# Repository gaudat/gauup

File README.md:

# Gaudat's GauUp
---

A collection of my rambling (GauUping). Expect unstructured mind-dump with project-logging and blogging mixed in.

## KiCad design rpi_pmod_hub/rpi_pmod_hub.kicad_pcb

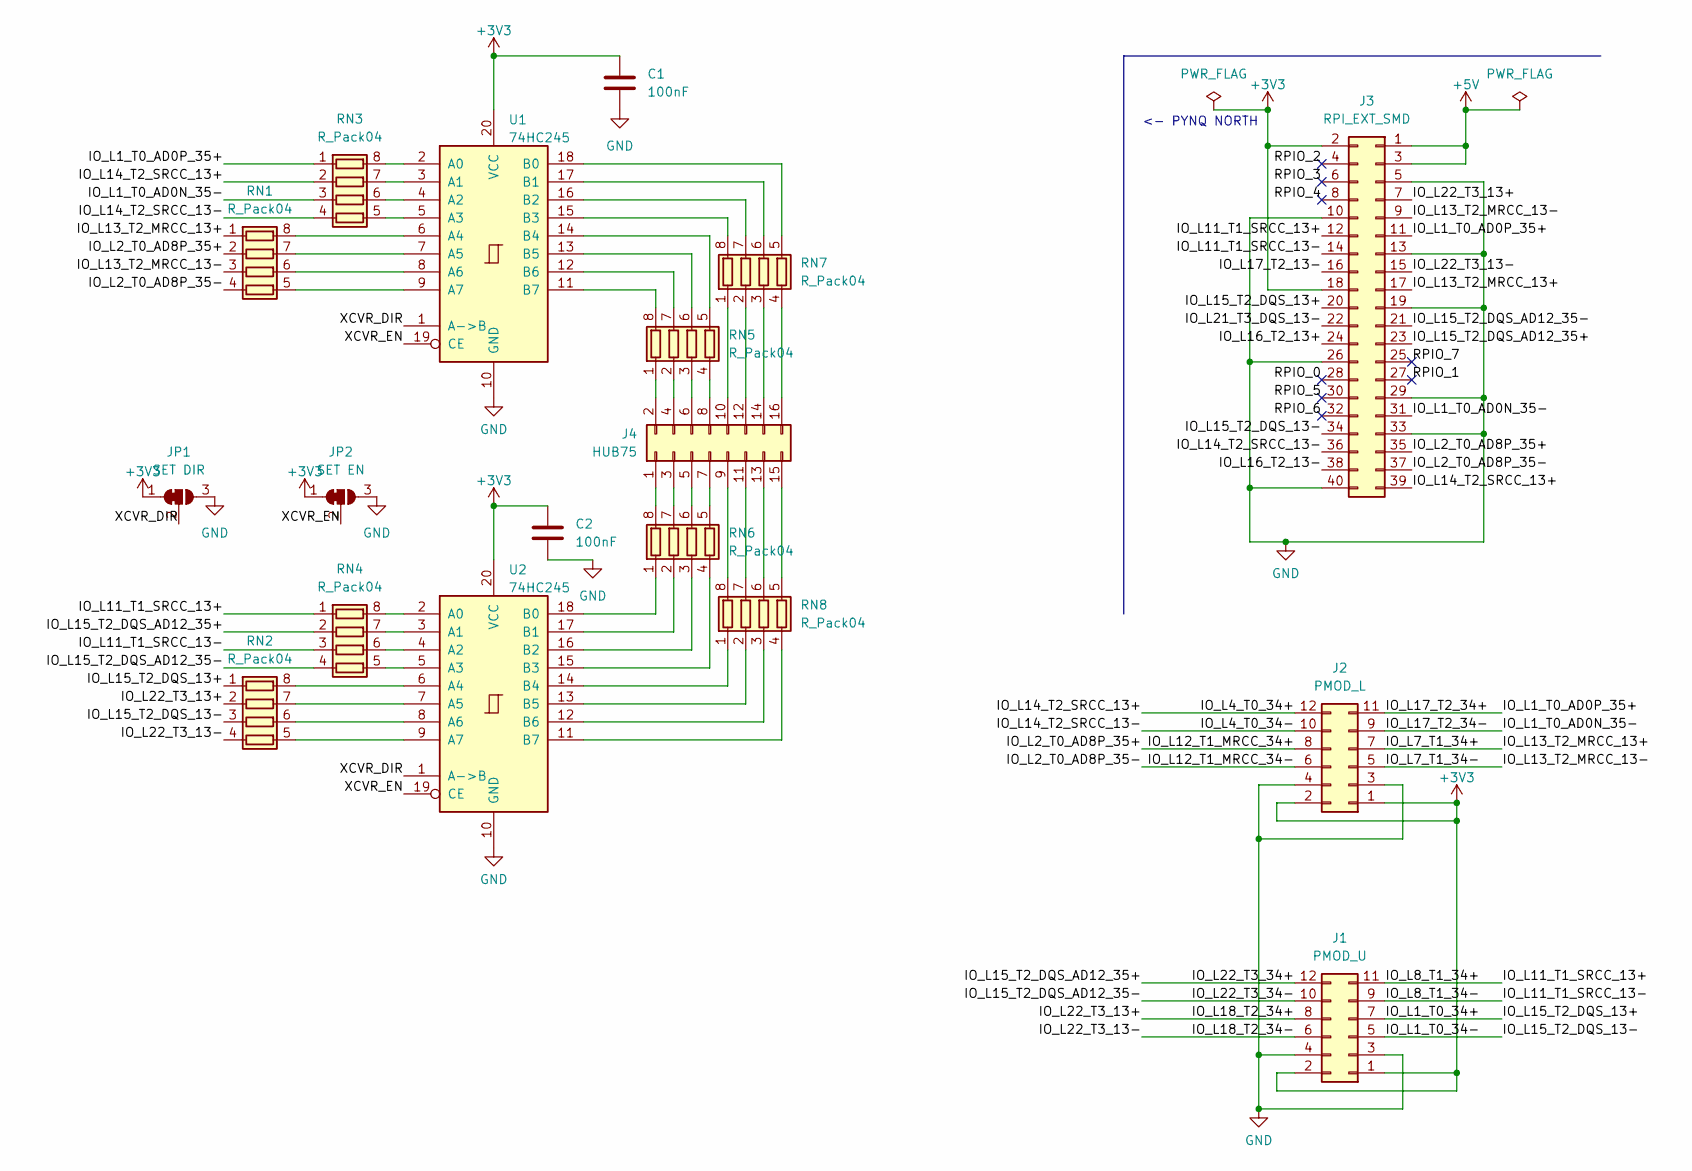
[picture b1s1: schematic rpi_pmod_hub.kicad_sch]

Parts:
C1, C2: 100nF; C_0603_1608Metric
J1: PMOD_U; PinHeader_2x06_P2.54mm_Horizontal
J2: PMOD_L; PinHeader_2x06_P2.54mm_Horizontal
J3: RPI_EXT_SMD; PinHeader_2x20_P2.54mm_Vertical_SMD
J4: HUB75; PinHeader_2x08_P2.54mm_Vertical_SMD
JP1: SET DIR; SolderJumper-3_P1.3mm_Bridged12_RoundedPad1.0x1.5mm_NumberL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
JP2: SET EN; SolderJumper-3_P1.3mm_Bridged12_RoundedPad1.0x1.5mm_NumberL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
RN1, RN2, RN3, RN4, RN5, RN6, RN7, RN8: R_Pack04; R_Array_Convex_4x0402
U1, U2: 74HC245; TSSOP-20_4.4x6.5mm_P0.65mm

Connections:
+3V3: C1.1, C2.1, J1.1, J1.2, J2.1, J2.2, J3.2, J3.18, JP1.1 (A), JP2.1 (A), U1.20 (VCC), U2.20 (VCC)
+5V: J3.1, J3.3
/IO_L11_T1_SRCC_13+: J1.11, J3.12, RN4.1 (R1.1)
/IO_L11_T1_SRCC_13-: J1.9, J3.14, RN4.3 (R3.1)
/IO_L12_T1_MRCC_34+: J2.8, J3.35, RN1.2 (R2.1)
/IO_L12_T1_MRCC_34-: J2.6, J3.37, RN1.4 (R4.1)
/IO_L13_T2_MRCC_13+: J2.7, J3.17, RN1.1 (R1.1)
/IO_L13_T2_MRCC_13-: J2.5, J3.9, RN1.3 (R3.1)
/IO_L14_T2_SRCC_13+: J2.12, J3.39, RN3.2 (R2.1)
/IO_L14_T2_SRCC_13-: J2.10, J3.36, RN3.4 (R4.1)
/IO_L15_T2_DQS_13+: J1.7, J3.20, RN2.1 (R1.1)
/IO_L15_T2_DQS_13-: J1.5, J3.34, RN2.3 (R3.1)
/IO_L15_T2_DQS_AD12_35+: J1.12, J3.23, RN4.2 (R2.1)
/IO_L15_T2_DQS_AD12_35-: J1.10, J3.21, RN4.4 (R4.1)
/IO_L16_T2_13+: J3.24
/IO_L16_T2_13-: J3.38
/IO_L17_T2_13-: J3.16
/IO_L17_T2_34+: J2.11, J3.11, RN3.1 (R1.1)
/IO_L17_T2_34-: J2.9, J3.31, RN3.3 (R3.1)
/IO_L18_T2_34+: J1.8, J3.7, RN2.2 (R2.1)
/IO_L18_T2_34-: J1.6, J3.15, RN2.4 (R4.1)
/IO_L21_T3_DQS_13-: J3.22
/RPIO_0: J3.28
/RPIO_1: J3.27
/RPIO_2: J3.4
/RPIO_3: J3.6
/RPIO_4: J3.8
/RPIO_5: J3.30
/RPIO_6: J3.32
/RPIO_7: J3.25
/XCVR_DIR: JP1.2 (C), U1.1 (A->B), U2.1 (A->B)
/XCVR_EN: JP2.2 (C), U1.19 (CE), U2.19 (CE)
GND: C1.2, C2.2, J1.3, J1.4, J2.3, J2.4, J3.5, J3.10, J3.13, J3.19, J3.26, J3.29, J3.33, J3.40, JP1.3 (B), JP2.3 (B), U1.10 (GND), U2.10 (GND)
unnamed: J4.1, RN6.8 (R1.2)
unnamed: J4.2, RN5.1 (R1.1)
unnamed: J4.3, RN6.7 (R2.2)
unnamed: J4.4, RN5.2 (R2.1)
unnamed: J4.5, RN6.6 (R3.2)
unnamed: J4.6, RN5.3 (R3.1)
unnamed: J4.7, RN6.5 (R4.2)
unnamed: J4.8, RN5.4 (R4.1)
unnamed: J4.9, RN8.8 (R1.2)
unnamed: J4.10, RN7.1 (R1.1)
unnamed: J4.11, RN8.7 (R2.2)
unnamed: J4.12, RN7.2 (R2.1)
unnamed: J4.13, RN8.6 (R3.2)
unnamed: J4.14, RN7.3 (R3.1)
unnamed: J4.15, RN8.5 (R4.2)
unnamed: J4.16, RN7.4 (R4.1)
unnamed: RN3.8 (R1.2), U1.2 (A0)
unnamed: RN3.7 (R2.2), U1.3 (A1)
unnamed: RN3.6 (R3.2), U1.4 (A2)
unnamed: RN3.5 (R4.2), U1.5 (A3)
unnamed: RN1.8 (R1.2), U1.6 (A4)
unnamed: RN1.7 (R2.2), U1.7 (A5)
unnamed: RN1.6 (R3.2), U1.8 (A6)
unnamed: RN1.5 (R4.2), U1.9 (A7)
unnamed: RN5.8 (R1.2), U1.11 (B7)
unnamed: RN5.7 (R2.2), U1.12 (B6)
unnamed: RN5.6 (R3.2), U1.13 (B5)
unnamed: RN5.5 (R4.2), U1.14 (B4)
unnamed: RN7.8 (R1.2), U1.15 (B3)
unnamed: RN7.7 (R2.2), U1.16 (B2)
unnamed: RN7.6 (R3.2), U1.17 (B1)
unnamed: RN7.5 (R4.2), U1.18 (B0)
unnamed: RN4.8 (R1.2), U2.2 (A0)
unnamed: RN4.7 (R2.2), U2.3 (A1)
unnamed: RN4.6 (R3.2), U2.4 (A2)
unnamed: RN4.5 (R4.2), U2.5 (A3)
unnamed: RN2.8 (R1.2), U2.6 (A4)
unnamed: RN2.7 (R2.2), U2.7 (A5)
unnamed: RN2.6 (R3.2), U2.8 (A6)
unnamed: RN2.5 (R4.2), U2.9 (A7)
unnamed: RN8.4 (R4.1), U2.11 (B7)
unnamed: RN8.3 (R3.1), U2.12 (B6)
unnamed: RN8.2 (R2.1), U2.13 (B5)
unnamed: RN8.1 (R1.1), U2.14 (B4)
unnamed: RN6.4 (R4.1), U2.15 (B3)
unnamed: RN6.3 (R3.1), U2.16 (B2)
unnamed: RN6.2 (R2.1), U2.17 (B1)
unnamed: RN6.1 (R1.1), U2.18 (B0)

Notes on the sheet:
<- PYNQ NORTH

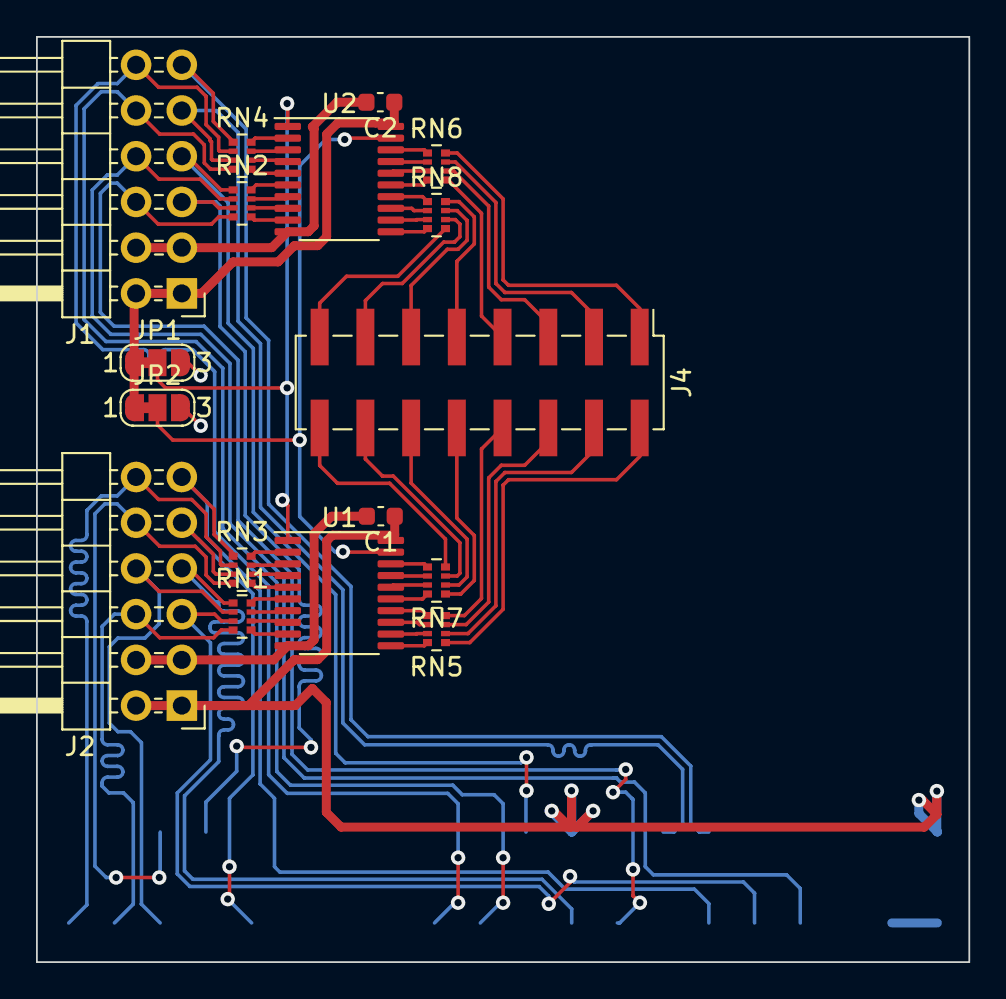
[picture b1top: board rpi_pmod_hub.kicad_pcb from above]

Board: 2 copper layers, 51.8 x 51.4 mm, 18 parts (1 on the bottom side), 69 nets.

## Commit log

2022-03-07 Add files
2022-03-13 Let there be light
2022-03-14 Move telegraph-css to its own folder
2022-03-14 Add "rlstatusbar"
2022-03-17 Add homelab 2022-03-10
2022-03-18 Update rlstatusbar
2022-04-01 Add scripts folder
2022-04-01 Add DDNS
2022-04-14 Recycled from swa
2022-05-16 Add esp_wifi_servo
2022-05-16 Add WiFi servo readme
2022-07-12 Add update_gallery_dl
2022-07-13 Add pve on wsl2
2022-07-13 Add pve networking
2022-07-16 Add sc scraper
2022-08-27 add sserdes
2022-09-07 Add rpi_pmod_hub
2022-09-07 WIP 20220907
2022-09-22 Add scrapers_px
2022-09-22 Add ediddetect
2022-09-23 WIP 20220923
2022-10-05 Add hub75
2022-10-05 Add hdl-util hdmi deep color mod. Not working.
2022-10-11 20221010 WIP
2022-11-03 Add n2pcecl
2022-11-10 Update bins
2022-11-11 Add oceb
2022-12-09 Add rdww
2023-01-23 add lre120
2023-01-30 Cleanup
2023-01-31 Add rlegen
2023-02-27 Add djc.bin
2023-05-15 Add bin
2025-09-27 Updated this years ago, forgot what it does
2025-09-27 Add sketch and scribble experiments
2025-09-27 --amend
